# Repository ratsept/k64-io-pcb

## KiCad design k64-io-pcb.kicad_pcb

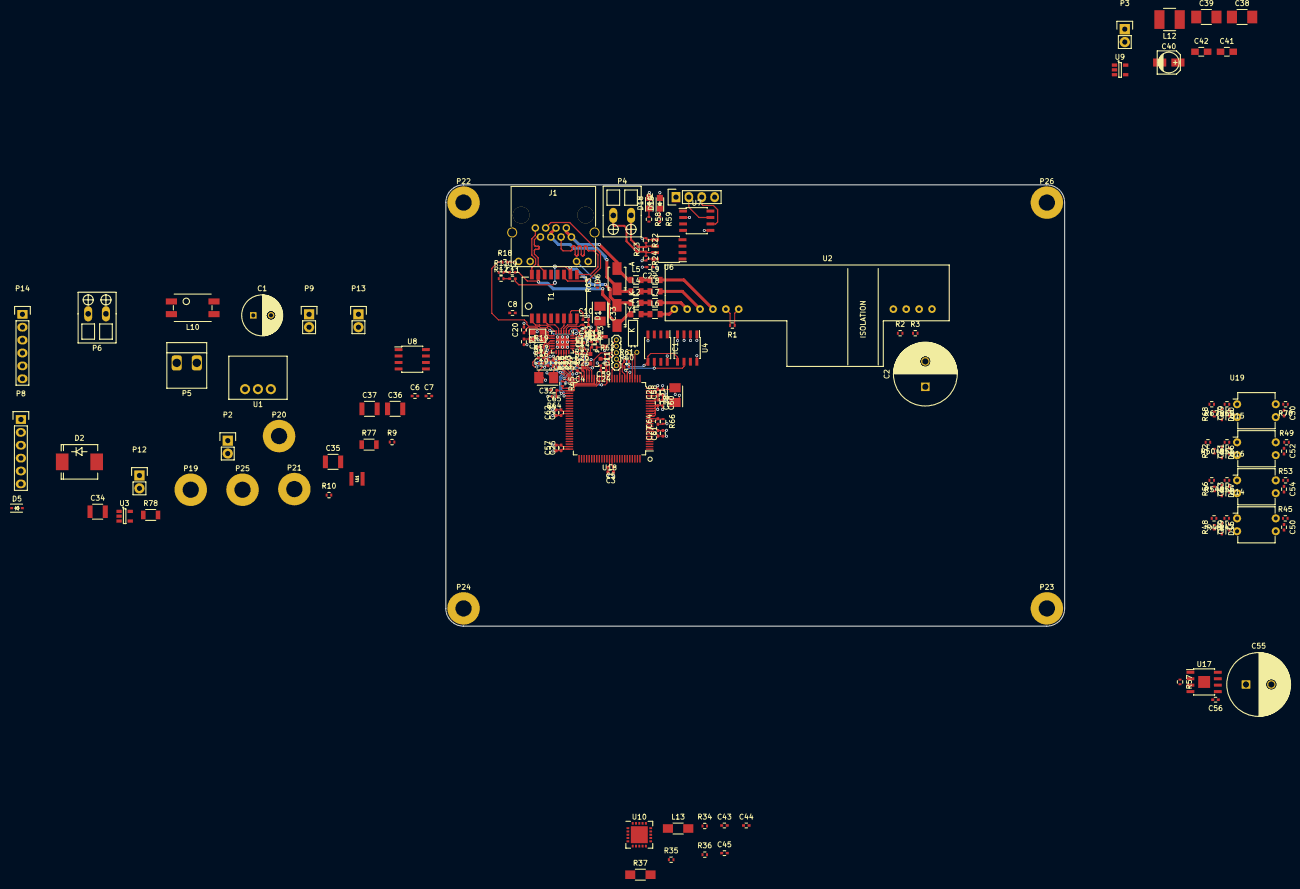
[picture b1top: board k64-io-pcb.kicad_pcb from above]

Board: 4 copper layers, 122.0 x 87.0 mm, 181 parts (0 on the bottom side), 125 nets.

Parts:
C1: 100u/50V; C_Radial_D8_L11.5_P3.5
C2, C55: 1000uF/50V; C_Radial_D12.5_L25_P5
C3, C8, C10, C13, C14, C16, C22, C43, C44, C45, C57, C58, C59, C60, C61, C62, C63, C65: 100n; C_0402
C4, C5, C9, C11, C23, C24, C25, C26, C27, C28: 1n; C_0402
C6, C7: 1u; C_0402
C12, C15, C17, C18, C64: 2u2; C_0402
C19: 100p; C_0402
C20, C21: 24p; C_0402
C29, C49, C51, C53, C56: 100n/50V; C_0402
C30, C50, C52, C54: 1u/6V3; C_0402
C31, C32, C33: 100u; TantalC_SizeB_EIA-3528_Reflow
C34, C35, C36, C37: 10u; C_1210
C38: 22u; C_1210_HandSoldering
C39: 4u7; C_1210_HandSoldering
C40: 47u; c_elec_4x5.3
C41: DNP; C_0805_HandSoldering
C42: 470p; C_0805_HandSoldering
D1, D6: D_TVS; Diode-SMA_Standard
D2: D_Schottky_Small; SMC_Standard
D5: Low I(rev); SOD-323
D11: D_Schottky_x2_ACom_AKK; SOT-23
D15, D16, D17, D20: ZENERsmall; SOD-323
D18, D19: Led_Small; LED_0805
IC1: FM24C64B; SOIC-8_3.9x4.9mm_Pitch1.27mm
J1: RJ45_LEDS_SHIELD; RJHSE538X
J2: CAN HEADER; Pin_Header_Straight_1x04
L1, L2, L4, L5, L6, L7, L8, L9: L_Small; C_0805
L3: 10uH; R_0805
L10: COMMON-MODE-FILTER; DR331
L11: 33uH; ASPI-0315FS
L12: L_Small; NR4018_HandSoldering
L13: L_Small; R_1206_HandSoldering
P1: SWD HEADER; 1X05-1.27MM
P2, P12, P13: DBG HEADER; Pin_Header_Straight_1x02
P3: CONN_01X02; Pin_Header_Straight_1x02
P4: RS-485; Phoenix_SMKDS_2pin
P5: EXT SUPPLY OUTPUT; JST_VH_3.96mm_2pin
P6: RESERVE POWER OUTPUT; Phoenix_SMKDS_2pin
P8: SPI HEADER; Pin_Header_Straight_1x06
P9: I2C HEADER; Pin_Header_Straight_1x02
P14: Debug serial; Pin_Header_Straight_1x06
P19, P20, P21, P22, P23, P24, P25, P26: CONN_01X01; MountingHole_3.2mm_M3_Pad
R1, R2, R3, R13: DNP; R_0402
R9, R48, R52, R56, R68: 100k; R_0402
R10, R14, R34, R35, R36, R66: 10k; R_0402
R11, R12: 75R; R_0402
R15, R16, R17, R20, R21, R25, R26, R27: 33R; R_0402
R18, R58, R59, R63: 100R; R_0402
R19: 6k49; R_0402
R22, R24: 680R; R_0402
R23: 120R; R_0402
R37: 400R 0.1%; R_1206_HandSoldering
R45, R46, R47, R49, R50, R51, R53, R54, R55, R67, R69, R70: 1k; R_0402
R57: 32K; R_0402
R60, R61, R62, R64: 4k7; R_0402
R65: 0; R_0402
R77, R78: DNP; R_1206
T1: eth_magnetics; WE-749010013
U1: R-78E-1.0
U2: Ag9700-FL; Ag9700-sil
U3: opamp; SOT-23-5
U4: AT24MAC402; SOIC-8_3.9x4.9mm_Pitch1.27mm
U5: KSZ8081RNACA_QFN-24; QFN-24-1EP_4x4mm_Pitch0.5mm
U6: SN65HVD72DR; SOIC-8_3.9x4.9mm_Pitch1.27mm
U7: CAN_transceiver; SOIC-8_3.9x4.9mm_Pitch1.27mm
U8: LM2931; SOIC-8_3.9x4.9mm_Pitch1.27mm
U9: LMR62421; SOT-23-5
U10: MAX31865; QFN-20-1EP_5x5mm_Pitch0.65mm
U14, U15, U16, U19: ?; DIP-4_W7.62mm
U17: DRV8871DDAR; SOIC-8-1EP_3.9x4.9mm_Pitch1.27mm
U18: MK64FN1M0VLL12TQFP100_LQFP100; LQFP-100_14x14mm_Pitch0.5mm
X1: 25MHz; crystal_FA238-TSX3225
Y1: 32.768KHz; Crystal_Round_Horizontal_2mm

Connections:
+3V3: C3.1, C4.1, C5.1, C6.1, C15.1, C16.1, C22.1, C23.1, C24.1, C25.1, C26.1, C27.1, C28.1, C31.1, C32.1, C43.1, C57.1, C58.1, C59.1, C60.1, C61.1, C62.1, C63.1, D5.1, D11.2, D18.2, D19.2, IC1.8, J1.10, J1.12, L3.1, L13.2, P1.3, P12.1, R13.2, R14.2, R24.2, R34.1, R35.1, R36.1, R45.2, R49.2, R53.2, R60.2, R61.2, R62.2, R64.2, R70.2, U1.3, U3.5, U4.8, U5.14, U6.8, U7.5, U10.19, U18.8, U18.22, U18.23, U18.30, U18.40, U18.48, U18.61, U18.75, U18.89
+5V: C7.1, P2.1, U7.3, U8.1
+12V: C1.1, C2.1, C34.2, C55.1, C56.1, D2.2, J2.4, L10.3, L11.1, P13.1, R2.2, R9.1, U2.8, U8.8, U17.5
/CS0: P8.4, R35.2, U10.13, U18.93
/CS1: P8.5, U18.97
/CS2: P8.6, U18.98
/DRV8871 DC Motor Driver/DC_IN1: U17.3, U18.72
/DRV8871 DC Motor Driver/DC_IN2: U17.2, U18.73
/MBUS/MBus_V+: C38.1, L12.1, U9.5
/MBUS/MBus_Vout: C39.1, C40.1, C42.1, P3.2
/MCU/3G_ON: P14.2, U18.35
/MCU/CAN_RX: U7.4, U18.65
/MCU/CAN_STBY: U7.8, U18.66
/MCU/CAN_TX: U7.1, U18.64
/MCU/DENABLE: U6.2, U6.3, U18.7
/MCU/ETH_PHY_RST: D11.3, R62.1, U18.38
/MCU/IO1: C50.1, R45.1, U14.4, U18.57
/MCU/IO2: C52.1, R49.1, U15.4, U18.58
/MCU/IO3: C54.1, R53.1, U16.4, U18.59
/MCU/IO4: C30.1, R70.1, U18.62, U19.4
/MCU/LINK_LED: J1.11, R63.2
/MCU/RMII_CRS_DV: R20.2, U18.44
/MCU/RMII_MDC: U5.11, U18.54
/MCU/RMII_MDIO: U5.10, U18.53
/MCU/RMII_RXCLK: R21.2, U18.50
/MCU/RMII_RXD0: R16.1, U18.43
/MCU/RMII_RXD1: R17.1, U18.42
/MCU/RMII_RXER: R15.1, U18.39
/MCU/RMII_TXD0: R26.1, U18.46
/MCU/RMII_TXD1: R27.1, U18.47
/MCU/RMII_TXEN: R25.1, U18.45
/MCU/SWDCLK: P1.2, U18.34
/MCU/SWDIO: P1.1, U18.37
/MCU/UART1_CTS: P14.4, U18.3
/MCU/UART1_RTS: P14.3, U18.4
/MCU/UART1_RX: P14.6, U18.2
/MCU/UART1_TX: P14.5, U18.1
/MCU/V_SUPPLY_ADC: U3.1, U3.4, U18.56
/MCU/~MCU_RESET: C65.1, P1.5, R64.1, U18.52
/MISO: P8.1, U10.14, U18.96
/MOSI: P8.2, R36.2, U10.11, U18.95
/RS-485/A: P4.1, R22.2, R23.2, U6.6
/RS-485/B: P4.2, R23.1, R24.1, U6.7
/RS-485/DI: U6.4, U18.5
/RS-485/RO: U6.1, U18.6
/SCK: P8.3, R34.2, U10.12, U18.94
/SCL: IC1.6, P9.2, R60.1, U4.6, U18.31
/SDA: IC1.5, P9.1, R61.1, U4.5, U18.32
/ethernet/ETH_LED: J1.9, R18.2
/ethernet/RD_N: T1.8, U5.3
/ethernet/RD_P: T1.6, U5.4
/ethernet/RX+: J1.3, T1.11
/ethernet/RX-: J1.6, T1.9
/ethernet/TD_N: T1.3, U5.5
/ethernet/TD_P: T1.1, U5.6
/ethernet/TX+: J1.1, T1.16
/ethernet/TX-: J1.2, T1.14
/ethernet/VA1: C9.2, D1.1, L1.1, T1.15
/ethernet/VA2: C11.2, D1.2, L2.1, T1.10
/ethernet/VB1: D6.1, J1.4, J1.5, L4.1
/ethernet/VB2: D6.2, J1.7, J1.8, L5.1
Earth_Protective: C36.2, C37.1, J1.13, P19.1, P20.1, P21.1, P22.1, P23.1, P24.1, P25.1, P26.1, R11.1, R12.1, R77.1, R78.1
GND: C1.2, C2.2, C3.2, C4.2, C5.2, C6.2, C7.2, C8.2, C10.2, C12.1, C13.1, C14.1, C15.2, C16.2, C17.1, C18.2, C19.2, C20.2, C21.2, C22.2, C23.2, C24.2, C25.2, C26.2, C27.2, C28.2, C29.1, C30.2, C31.2, C32.2, C33.1, C34.1, C35.1, C38.2, C39.2, C40.2, C41.2, C43.2, C44.1, C49.1, C50.2, C51.1, C52.2, C53.1, C54.2, C55.2, C56.2, C57.2, C58.2, C59.2, C60.2, C61.2, C62.2, C63.2, C64.1, C65.2, D15.2, D16.2, D17.2, D20.2, IC1.4, J2.1, L10.4, P1.4, P2.2, P6.2, P12.2, P13.2, P14.1, R3.2, R10.2, R19.1, R22.1, R48.1, R52.1, R56.1, R57.1, R65.1, R66.2, R68.1, R77.2, R78.2, U1.2, U2.7, U3.2, U4.1, U4.2, U4.3, U4.4, U5.22, U5.25, U6.5, U7.2, U8.2, U8.3, U8.6, U8.7, U9.2, U10.10, U10.15, U10.16, U10.21, U14.2, U14.3, U15.2, U15.3, U16.2, U16.3, U17.1, U17.7, U17.9, U18.9, U18.14, U18.15, U18.16, U18.17, U18.18, U18.19, U18.20, U18.21, U18.24, U18.25, U18.41, U18.49, U18.60, U18.74, U18.88, U19.2, U19.3, X1.3
unnamed: C8.1, T1.2
unnamed: C9.1, R11.2
unnamed: C10.1, T1.7
unnamed: C11.1, R12.2
unnamed: C12.2, C13.2, C33.2, L3.2, R13.1, U5.2
unnamed: C14.2, C17.2, U5.1
unnamed: C18.1, D11.1, R14.1, U5.24
unnamed: C19.1, R19.2, U5.9
unnamed: C20.1, U5.7, X1.1
unnamed: C21.1, U5.8, X1.2
unnamed: C29.2, D20.1, R67.1, R68.2, R69.2
unnamed: C35.2, L11.2, U1.1
unnamed: C36.1, P5.1
unnamed: C37.2, P5.2
unnamed: C41.1, C42.2, U9.3
unnamed: C44.2, L13.1, U10.20
unnamed: C45.1, U10.7
unnamed: C45.2, U10.8
unnamed: C49.2, D15.1, R46.1, R47.2, R48.2
unnamed: C51.2, D16.1, R50.1, R51.2, R52.2
unnamed: C53.2, D17.1, R54.1, R55.2, R56.2
unnamed: C64.2, R66.1, U18.12, U18.13
unnamed: D2.1, P6.1
unnamed: L12.2, U9.1
unnamed: D5.2, R9.2, R10.1, U3.3
unnamed: D18.1, R58.1
unnamed: D19.1, R59.1
unnamed: J2.2, U7.7
unnamed: J2.3, U7.6
unnamed: L1.2, L6.1
unnamed: L2.2, L7.1
unnamed: L4.2, L8.1
unnamed: L5.2, L9.1
unnamed: L6.2, U2.1
unnamed: L7.2, U2.2
unnamed: L8.2, U2.3
unnamed: L9.2, U2.4
unnamed: R1.1, U2.6
unnamed: R1.2, U2.5
unnamed: R2.1, R3.1, U2.9
unnamed: R15.2, U5.17
unnamed: R16.2, U5.13
unnamed: R17.2, U5.12
unnamed: R18.1, U5.23
unnamed: R20.1, U5.15
unnamed: R21.1, U5.16
unnamed: R25.2, U5.19
unnamed: R26.2, U5.20
unnamed: R27.2, U5.21
unnamed: R37.1, U10.1, U10.2
unnamed: R37.2, U10.3, U10.4
unnamed: R47.1, U14.1
unnamed: R51.1, U15.1
unnamed: R55.1, U16.1
unnamed: R57.2, U17.4
unnamed: R58.2, U18.100
unnamed: R59.2, U18.99
unnamed: R63.1, U18.55
unnamed: R65.2, U18.51
unnamed: R69.1, U19.1
unnamed: U18.28, Y1.2
unnamed: U18.29, Y1.1
